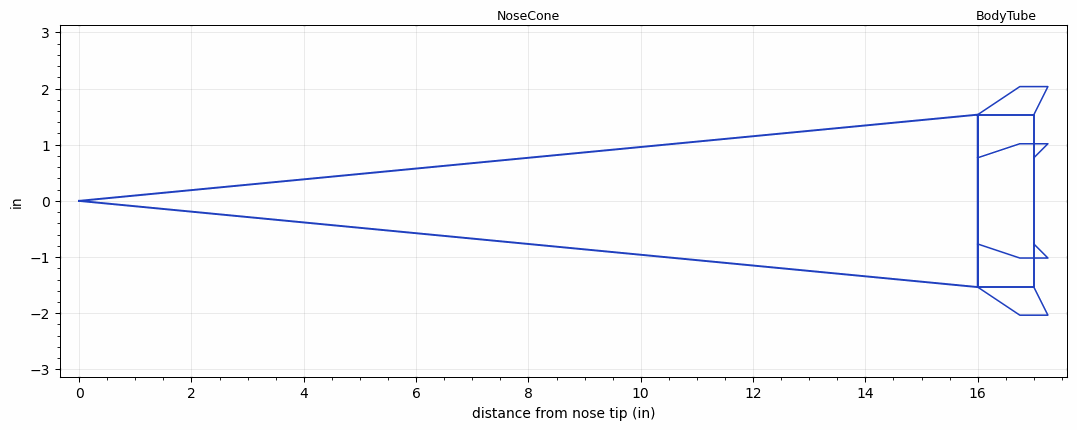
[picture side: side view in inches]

<RASAeroDocument>
 <FileVersion>2</FileVersion>
 <RocketDesign>
  <NoseCone>
   <Length>16</Length>
   <Diameter>3.07</Diameter>
   <Shape>Conical</Shape>
   <Location>0</Location>
  </NoseCone>
  <BodyTube>
   <Length>1</Length>
   <Diameter>3.07</Diameter>
   <Location>16</Location>
   <Fin>
    <Count>6</Count>
    <Chord>1</Chord>
    <Span>0.5</Span>
    <SweepDistance>0.75</SweepDistance>
    <TipChord>0.5</TipChord>
    <Thickness>0.125</Thickness>
    <Location>1</Location>
    <AirfoilSection>Square</AirfoilSection>
    <FX1>0.5</FX1>
    <FX3>0.5</FX3>
   </Fin>
  </BodyTube>
  <Surface>Smooth (Zero Roughness)</Surface>
  <ModifiedBarrowman>False</ModifiedBarrowman>
  <Turbulence>False</Turbulence>
  <UseBooster1>False</UseBooster1>
  <UseBooster2>False</UseBooster2>
 </RocketDesign>
 <LaunchSite>
  <Altitude>2000</Altitude>
  <Pressure>27.83</Pressure>
  <RodAngle>0</RodAngle>
  <RodLength>5</RodLength>
  <Temperature>51.87</Temperature>
  <WindSpeed>4.47</WindSpeed>
 </LaunchSite>
 <Recovery>
  <Altitude1>1000</Altitude1>
  <Altitude2>1000</Altitude2>
  <DeviceType1>None</DeviceType1>
  <DeviceType2>None</DeviceType2>
  <Event1>False</Event1>
  <Event2>False</Event2>
  <Size1>1</Size1>
  <Size2>1</Size2>
  <EventType1>None</EventType1>
  <EventType2>None</EventType2>
  <CD1>1.33</CD1>
  <CD2>1.33</CD2>
 </Recovery>
</RASAeroDocument>
